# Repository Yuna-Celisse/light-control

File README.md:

# light-control

基于 KiCad 10 的 fNIRS 光学采集与灯光控制板工程。

当前原理图主控为 STM32F103C8T6，包含 USB-C 与 ESD 保护、3.3 V 降压和 1.8 V 电源、ADS1115、双 AS7341 光谱传感器，以及板载双路光电接收与双波长 LED 驱动电路。光谱模块承担系统中的其他检测用途。

## 打开工程

1. 安装 KiCad 10。本次主控迁移检查使用 KiCad 10.0.8。
2. 克隆仓库并打开 `light-control.kicad_pro`。
3. 通过项目管理器打开原理图和 PCB。
4. 安装 KiCad 标准符号及封装库。项目自定义库通过 `${KIPRJMOD}` 相对路径加载。此次新注册的部分标准库仍引用本机其他工程路径，迁移环境时须重新配置库路径。

## 文件结构

|路径|内容|
|---|---|
|`light-control.kicad_pro`|KiCad 项目|
|`light-control.kicad_sch`|顶层原理图|
|`01_*.kicad_sch` 至 `10_*.kicad_sch`|十张在用功能子页，主控使用 `03_stm32f103.kicad_sch`|
|`light-control.kicad_pcb`|四层 PCB，全板布线、铺铜与器件特性隐患修复已完成，待导出制板文件|
|`light-control.kicad_dru`|自定义设计规则|
|`FNIRS.pretty`、`Lights_Edge.pretty`|自定义封装|
|`FNIRS.kicad_sym`、`light-control-custom.kicad_sym`|自定义符号|
|`docs/review-2026-11-10.md`|设计变更、隐患修复与打样复核记录|
|`docs/checks`|检查证据（`drc.json`、`erc.json`、`source-sha256.txt`），须核对生成时间与对应设计版本|

## 当前验证状态

2026-11-17 完成全板布线、元器件特性隐患排查、走线几何规范化（含 `/03_STM32F103/NRST` 环路与锐角清理）及独立设计评审复核（当前包含 164 个器件、1459 段走线、223 个过孔、3 个铺铜区，`In1.Cu` 保持完整地平面且无信号线穿越）：

- **隐患修复与走线规范化**：已移除 `L1`、`D101`、`D103` 器件隐患并消除孤立 `GND` 铜岛；全板各层消除非 45°/90° 折线段、裸铜锐角、过孔中心 90° 拐角、冗余共线分段与重叠线段，将 `silk_over_copper` 警告清零（12 → 0），并移除 `NRST` 处 `C18.1`—`R9.2`—过孔同层闭合铜环与 45° 锐角及 `In2.Cu` 微线段。
- **DRC / ERC 与可制造性**：重填铺铜并保存后，KiCad 10.0.8 实测 **DRC 0 错误、0 未连接项**（仅剩 4 项库差异/字段警告：`lib_footprint_mismatch` ×3 与 `Y1` 缺少 `C0 max` 字段的 `schematic_parity` ×1）；**ERC 0 错误**（27 项既有 `lib_symbol_mismatch` 警告）；`validate_for_manufacturing` 结论为 **`READY`**（可打样，PCBA/改版前建议补齐 `F.Cu`/`B.Cu` Mark 点与 `U5` MPN、将 1 颗 `0.2 mm` 过孔统一为 `0.3 mm`、补齐电源测试点并将 `U4.~FAULT` 接入 MCU）。

2026-11-11 完成十个模块内部布线、地铜补接及工程文件清理，随后补全模块间互连；SWD 使用六个长方形表面焊盘（1.5 × 3 mm、中心距 2 mm）。

2026-11-10 已将原理图主控迁移至 STM32F103C8T6，补齐 VDD、VDDA、VBAT 去耦、BOOT0/BOOT1、NRST、SWD 和 USB D+ 1.5 kΩ 上拉。两组 I²C 分别连接 ADS1115 与左光谱模块、右光谱模块。主控页使用 12 MHz HSE，PLL ×6 对应 72 MHz，USB 分频 1.5 对应 48 MHz。

晶振选用 ABM8W-12.0000MHZ-6-D1X-T3，C38/C39 初配 6 pF，寄生电容暂按 3 pF 估计，最终负载需结合完成后的 PCB 与实测校准。

模块连线整理阶段覆盖 11 张在用原理图，模块内部采用连续导线，模块之间采用网络标签。整理前后 164 个器件的型号、数值、封装与 UUID 一致，全部网络端点连接一致。逐页导线检查为 0 个悬空端点，全项目 ERC 为 0 个错误、27 个库符号差异警告。

迁移前后导出网表对比显示，主控块以外的业务模块间连接一致。删除 ESP32 专用 L2、L3、C36，新增 J2 调试接口，其余主控外围按 STM32 重新配置。

PCB 已同步最新原理图，含 164 个器件。155 个原器件的位置、角度与层完全沿用原布局，U5 沿用原中心并旋转 90°，7 颗主控外围器件做了避让微调。J2 按参考图改为靠近板边的一排长方形表面焊盘，距板边 0.6 mm，间距 2 mm，单焊盘 1.5 × 3 mm，顺序为 3V3、SWDIO、GND、SWCLK、NRST、GND。

最终 DRC/ERC 报告及核查明细见 [复核记录](docs/review-2026-11-10.md) 与 [`docs/checks/`](docs/checks)。

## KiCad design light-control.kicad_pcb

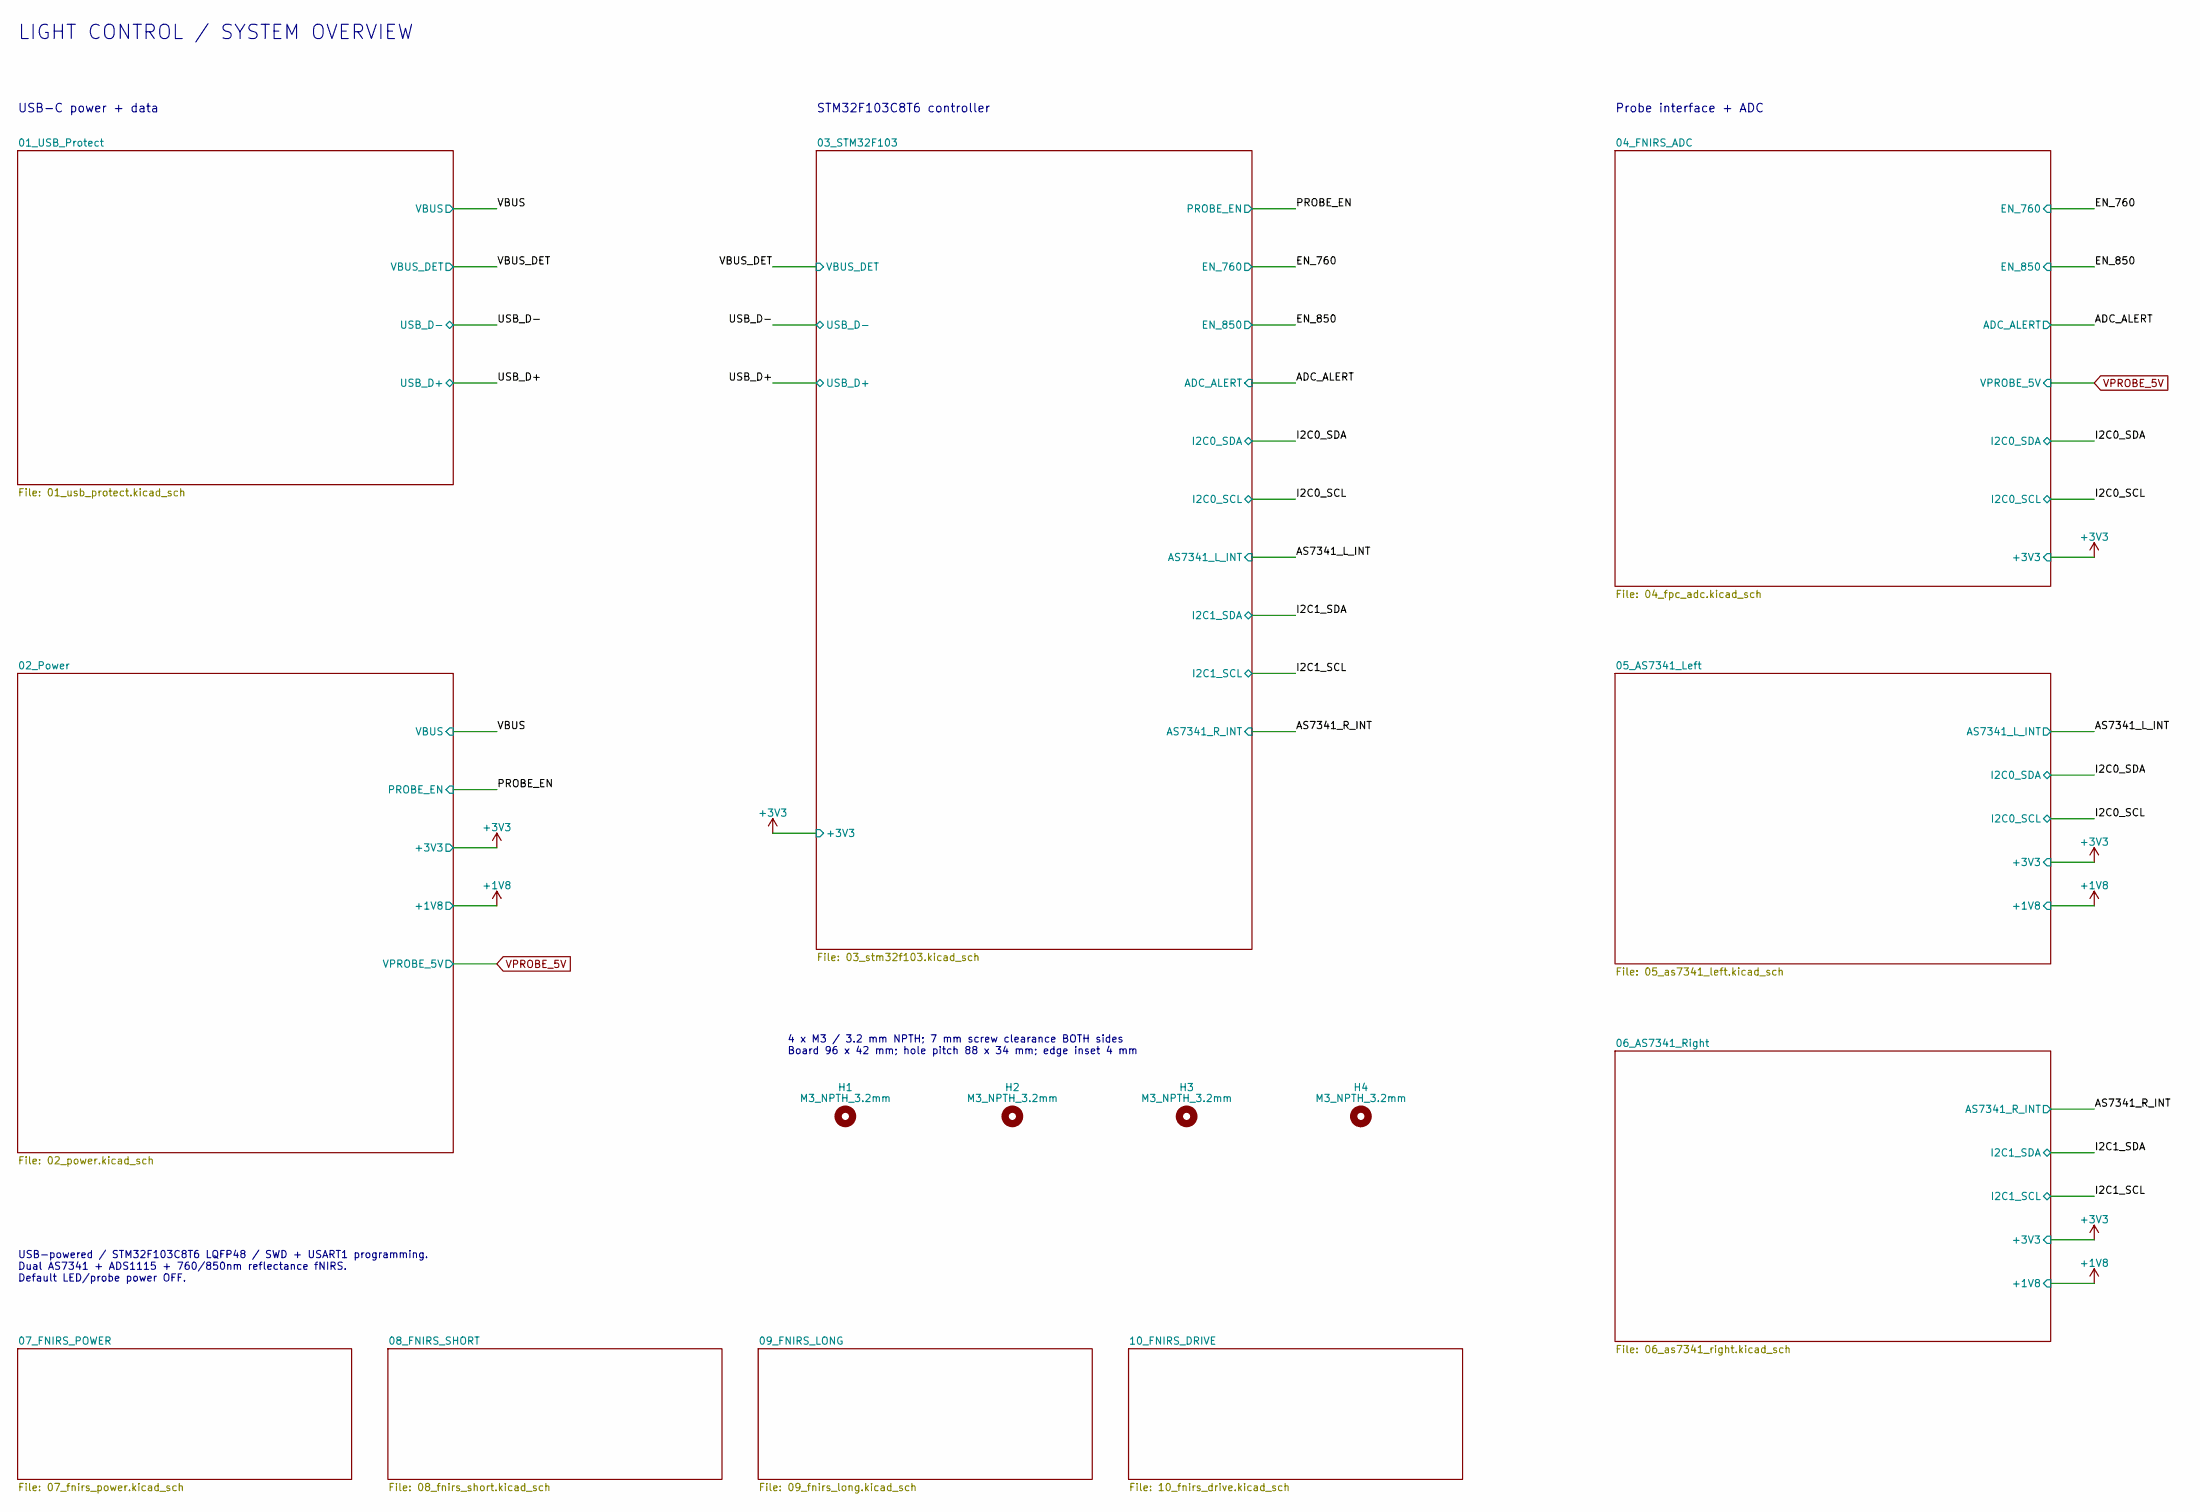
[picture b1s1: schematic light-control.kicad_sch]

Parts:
H1, H2, H3, H4: M3_NPTH_3.2mm; MountingHole_M3_3.2mm_Clearance7mm

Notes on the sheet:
LIGHT CONTROL / SYSTEM OVERVIEW
4 x M3 / 3.2 mm NPTH; 7 mm screw clearance BOTH sides Board 96 x 42 mm; hole pitch 88 x 34 mm; edge inset 4 mm
Probe interface + ADC
USB-C power + data
STM32F103C8T6 controller
USB-powered / STM32F103C8T6 LQFP48 / SWD + USART1 programming. Dual AS7341 + ADS1115 + 760/850nm reflectance fNIRS. Default LED/probe power OFF.

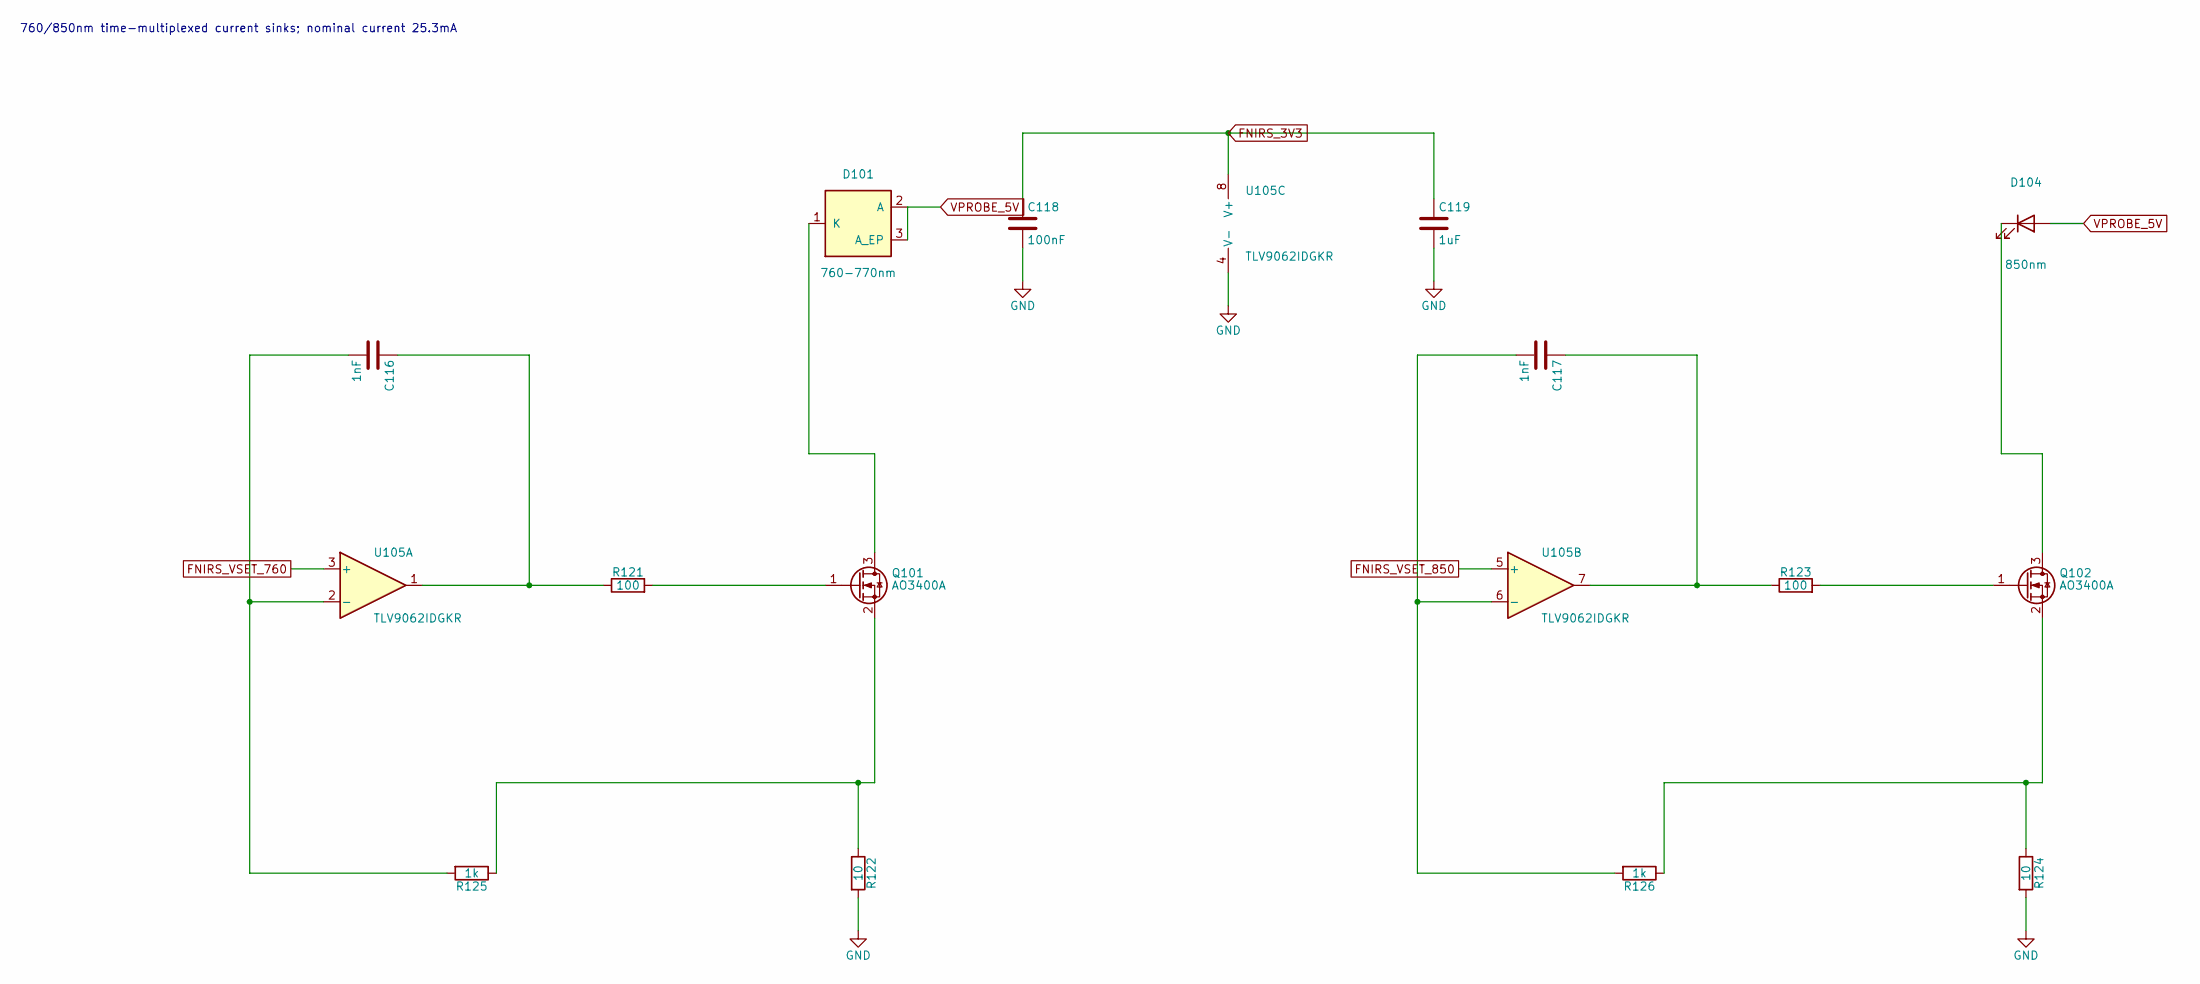
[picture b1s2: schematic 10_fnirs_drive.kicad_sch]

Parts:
C116, C117: 1nF; C_0603_1608Metric; MPN CL10C102JB8NNNC
C118: 100nF; C_0603_1608Metric
C119: 1uF; C_0603_1608Metric
D101: 760-770nm; JNJ_760_3535_3P; MPN JNJ-LEHR0113W120/42MIL/760-770NM
D104: 850nm; JNJ_850_3036_2P; MPN JNJ-LTJI0106W90/14mil-D/850NM
Q101, Q102: AO3400A; SOT-23; MPN AO3400A
R121, R123: 100; R_0603_1608Metric; MPN 0603WAF1000T5E
R122, R124: 10; R_0603_1608Metric; MPN 0603WAF100JT5E
R125, R126: 1k; R_0603_1608Metric; MPN 0603WAF1001T5E
U105: TLV9062IDGKR; VSSOP-8_3x3mm_P0.65mm; MPN TLV9062IDGKR

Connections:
FNIRS_3V3: C118.1, C119.1, U105.8 (V+); also elsewhere on the board
FNIRS_VSET_760: U105.3 (+); also elsewhere on the board
FNIRS_VSET_850: U105.5 (+); also elsewhere on the board
unnamed: C116.1, R121.1, U105.1
unnamed: C117.1, R123.1, U105.7
unnamed: D101.1 (K), Q101.3 (D)
unnamed: D104.1 (K), Q102.3 (D)
unnamed: Q101.1 (G), R121.2
unnamed: Q101.2 (S), R122.1, R125.1
unnamed: Q102.1 (G), R123.2
unnamed: Q102.2 (S), R124.1, R126.1
unnamed: C116.2, R125.2, U105.2 (-)
unnamed: C117.2, R126.2, U105.6 (-)
VPROBE_5V: D101.2 (A), D101.3 (A_EP), D104.2 (A); also elsewhere on the board

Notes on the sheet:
760/850nm time-multiplexed current sinks; nominal current 25.3mA

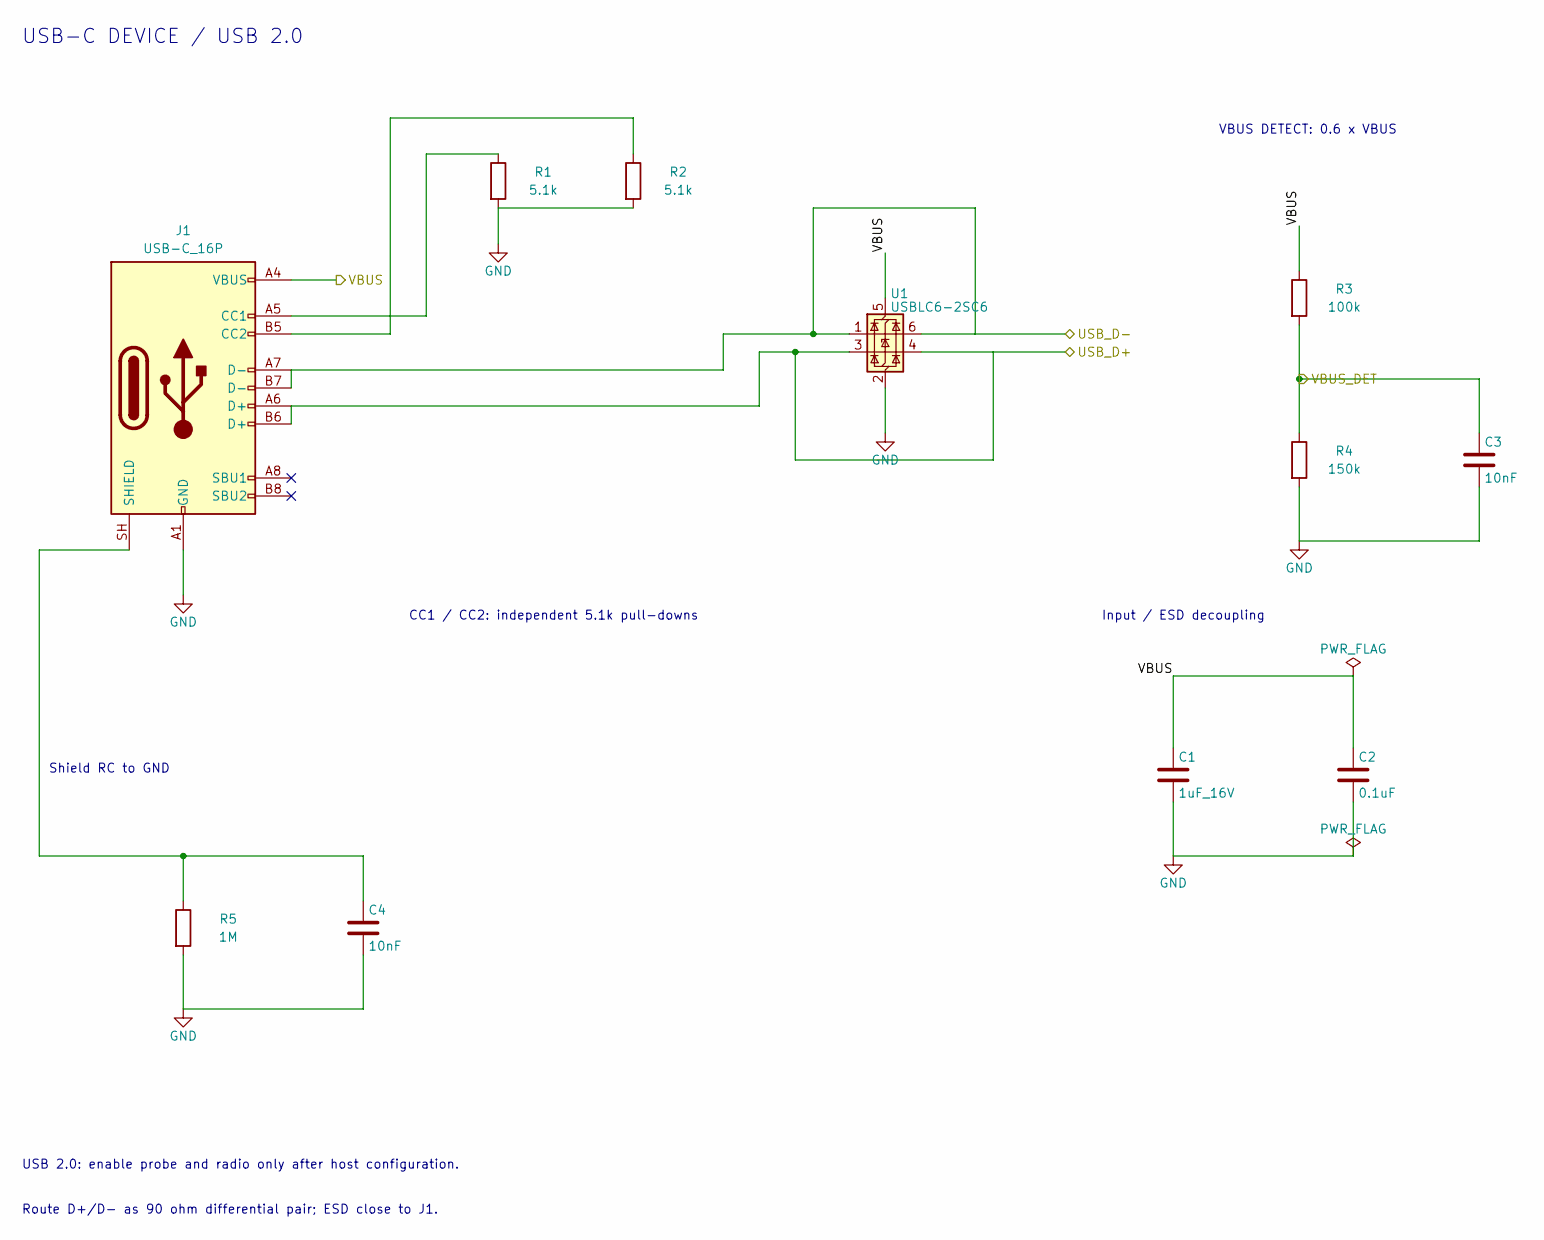
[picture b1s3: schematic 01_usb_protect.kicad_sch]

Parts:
C1: 1uF_16V; C_0603_1608Metric
C2: 0.1uF; C_0402_1005Metric
C3: 10nF; C_0402_1005Metric
C4: 10nF; C_0603_1608Metric
J1: USB-C_16P; USB_C_Receptacle_HRO_TYPE-C-31-M-12
R1, R2: 5.1k; R_0402_1005Metric
R3: 100k; R_0402_1005Metric
R4: 150k; R_0402_1005Metric
R5: 1M; R_0603_1608Metric
U1: USBLC6-2SC6; SOT-23-6; MPN USBLC6-2SC6

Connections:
/USB_D+: J1.A6 (D+), J1.B6 (D+), U1.3 (I/O2), U1.4 (I/O2); also elsewhere on the board
/USB_D-: J1.A7 (D-), J1.B7 (D-), U1.1 (I/O1), U1.6 (I/O1); also elsewhere on the board
/VBUS_DET: C3.1, R3.2, R4.1; also elsewhere on the board
unnamed: J1.A5 (CC1), R1.1
unnamed: J1.B5 (CC2), R2.1
unnamed: C4.1, J1.SH (SHIELD), R5.1

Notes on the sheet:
Shield RC to GND
VBUS DETECT: 0.6 x VBUS
USB-C DEVICE / USB 2.0
CC1 / CC2: independent 5.1k pull-downs
Input / ESD decoupling
Route D+/D- as 90 ohm differential pair; ESD close to J1.
USB 2.0: enable probe and radio only after host configuration.

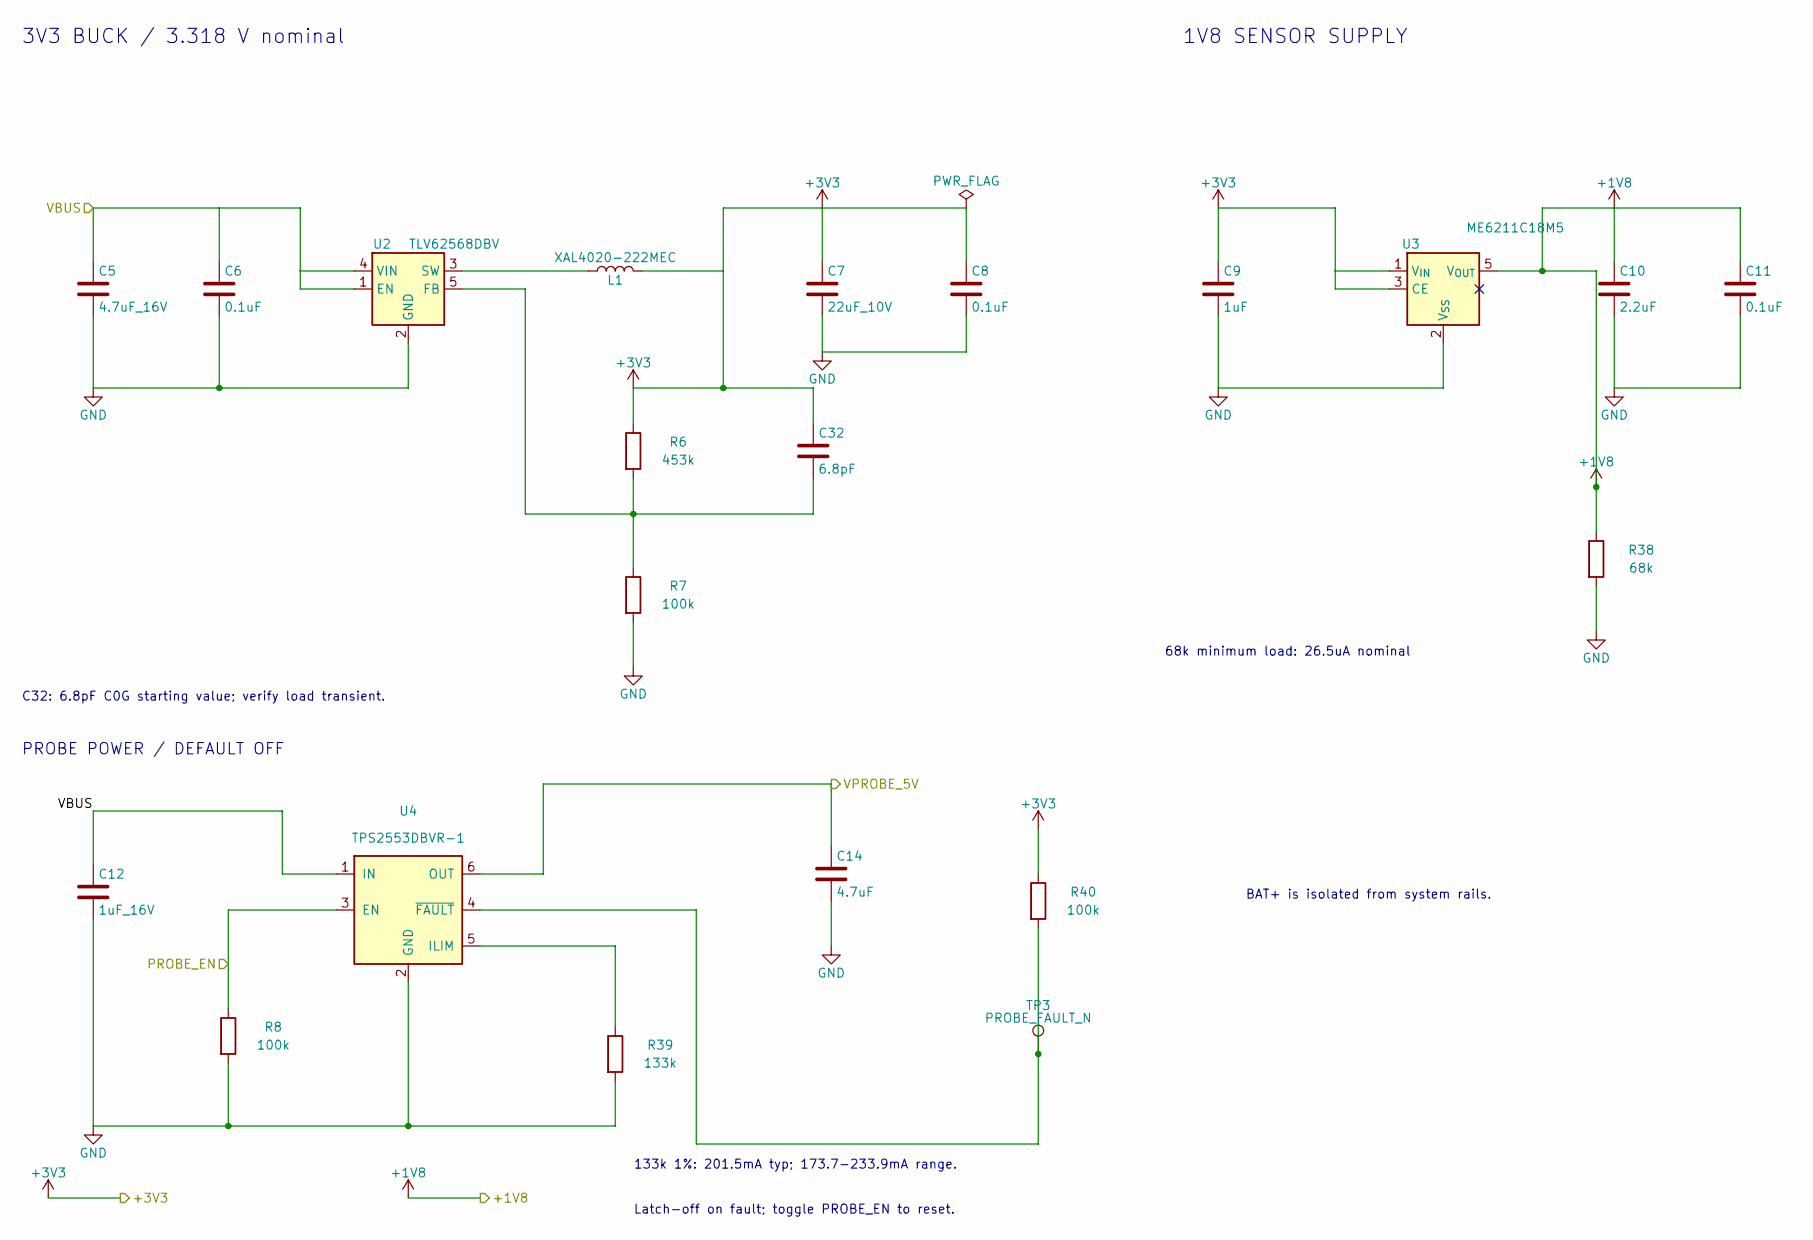
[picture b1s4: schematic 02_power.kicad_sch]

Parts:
C5: 4.7uF_16V; C_0805_2012Metric
C6, C8, C11: 0.1uF; C_0402_1005Metric
C7: 22uF_10V; C_0805_2012Metric
C9: 1uF; C_0402_1005Metric
C10: 2.2uF; C_0603_1608Metric
C12: 1uF_16V; C_0402_1005Metric
C14: 4.7uF; C_0603_1608Metric
C32: 6.8pF; C_0402_1005Metric; Tolerance 5%
L1: XAL4020-222MEC; L_Coilcraft_XAL4020-XXX
R6: 453k; R_0402_1005Metric
R7, R8, R40: 100k; R_0402_1005Metric
R38: 68k; R_0402_1005Metric; Tolerance 1%
R39: 133k; R_0402_1005Metric; Tolerance 1%
TP3: PROBE_FAULT_N; TestPoint_Pad_D1.0mm
U2: TLV62568DBV; SOT-23-5; MPN TLV62568DBVR
U3: ME6211C18M5; SOT-23-5; MPN ME6211C18M5
U4: TPS2553DBVR-1; SOT-23-6; MPN TPS2553DBVR-1

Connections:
+1V8: C10.1, C11.1, R38.1, U3.5 (V_{OUT}); also elsewhere on the board
+3V3: C7.1, C8.1, C9.1, C32.1, L1.2, R6.1, R40.1, U3.1 (V_{IN}), U3.3 (CE); also elsewhere on the board
/PROBE_EN: R8.1, U4.3 (EN); also elsewhere on the board
unnamed: C32.2, R6.2, R7.1, U2.5 (FB)
unnamed: L1.1, U2.3 (SW)
unnamed: R39.1, U4.5 (ILIM)
unnamed: R40.2, TP3.1 (1_1), U4.4 (~FAULT)
VPROBE_5V: C14.1, U4.6 (OUT); also elsewhere on the board

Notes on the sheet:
3V3 BUCK / 3.318 V nominal
BAT+ is isolated from system rails.
Latch-off on fault; toggle PROBE_EN to reset.
C32: 6.8pF C0G starting value; verify load transient.
PROBE POWER / DEFAULT OFF
133k 1%: 201.5mA typ; 173.7-233.9mA range.
68k minimum load: 26.5uA nominal
1V8 SENSOR SUPPLY

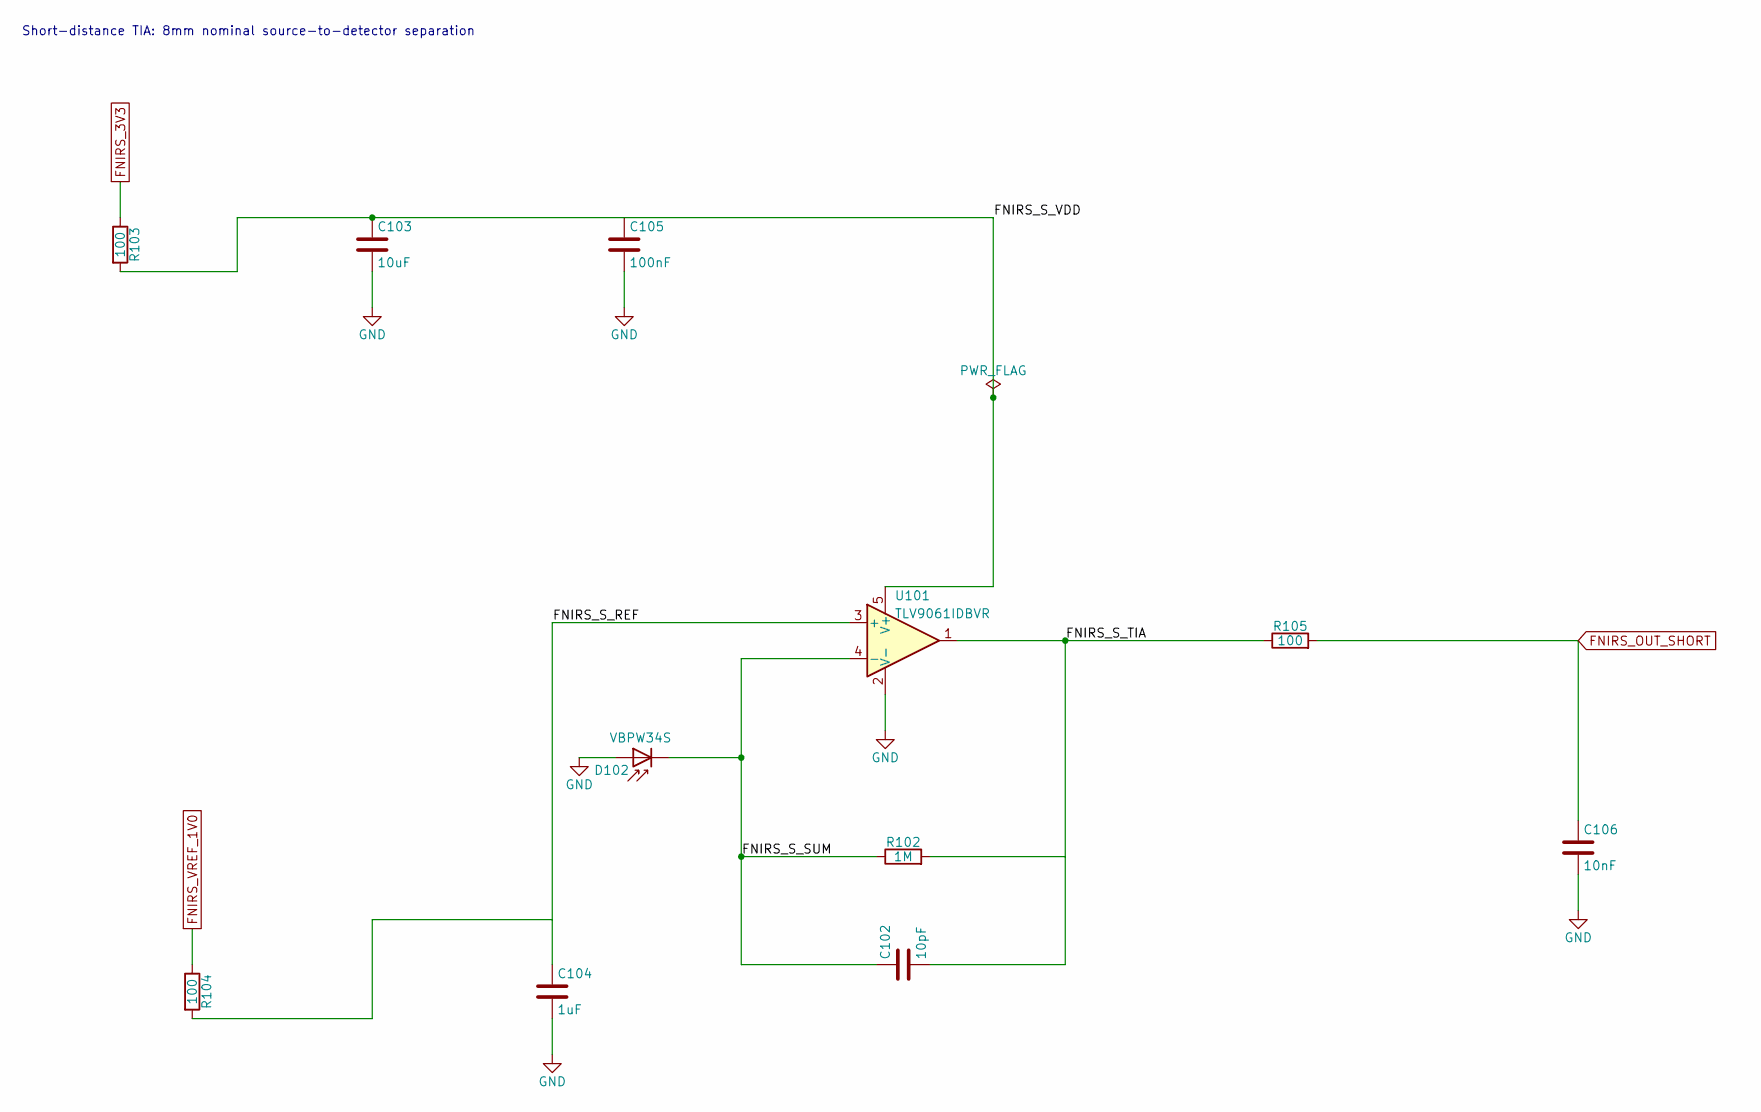
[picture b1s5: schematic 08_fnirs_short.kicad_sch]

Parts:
C102: 10pF; C_0603_1608Metric; MPN CL10C100JB8NNNC
C103: 10uF; C_0805_2012Metric; MPN CL21A106KAYNNNE
C104: 1uF; C_0603_1608Metric; MPN CL10A105KB8NNNC
C105: 100nF; C_0603_1608Metric; MPN CC0603KRX7R9BB104
C106: 10nF; C_0603_1608Metric; MPN 0603B103K500NT
D102: VBPW34S; VBPW34S_Normal_Gullwing; MPN VBPW34S
R102: 1M; R_0603_1608Metric; MPN 0603WAF1004T5E
R103, R104, R105: 100; R_0603_1608Metric; MPN 0603WAF1000T5E
U101: TLV9061IDBVR; SOT-23-5; MPN TLV9061IDBVR

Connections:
/08_FNIRS_SHORT/FNIRS_S_REF: C104.1, R104.2, U101.3 (+)
/08_FNIRS_SHORT/FNIRS_S_SUM: C102.1, D102.1 (K), R102.1, U101.4 (-)
/08_FNIRS_SHORT/FNIRS_S_TIA: C102.2, R102.2, R105.1, U101.1
/08_FNIRS_SHORT/FNIRS_S_VDD: C103.1, C105.1, R103.2, U101.5 (V+)
FNIRS_3V3: R103.1; also elsewhere on the board
FNIRS_OUT_SHORT: C106.1, R105.2; also elsewhere on the board
FNIRS_VREF_1V0: R104.1; also elsewhere on the board

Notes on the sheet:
Short-distance TIA: 8mm nominal source-to-detector separation

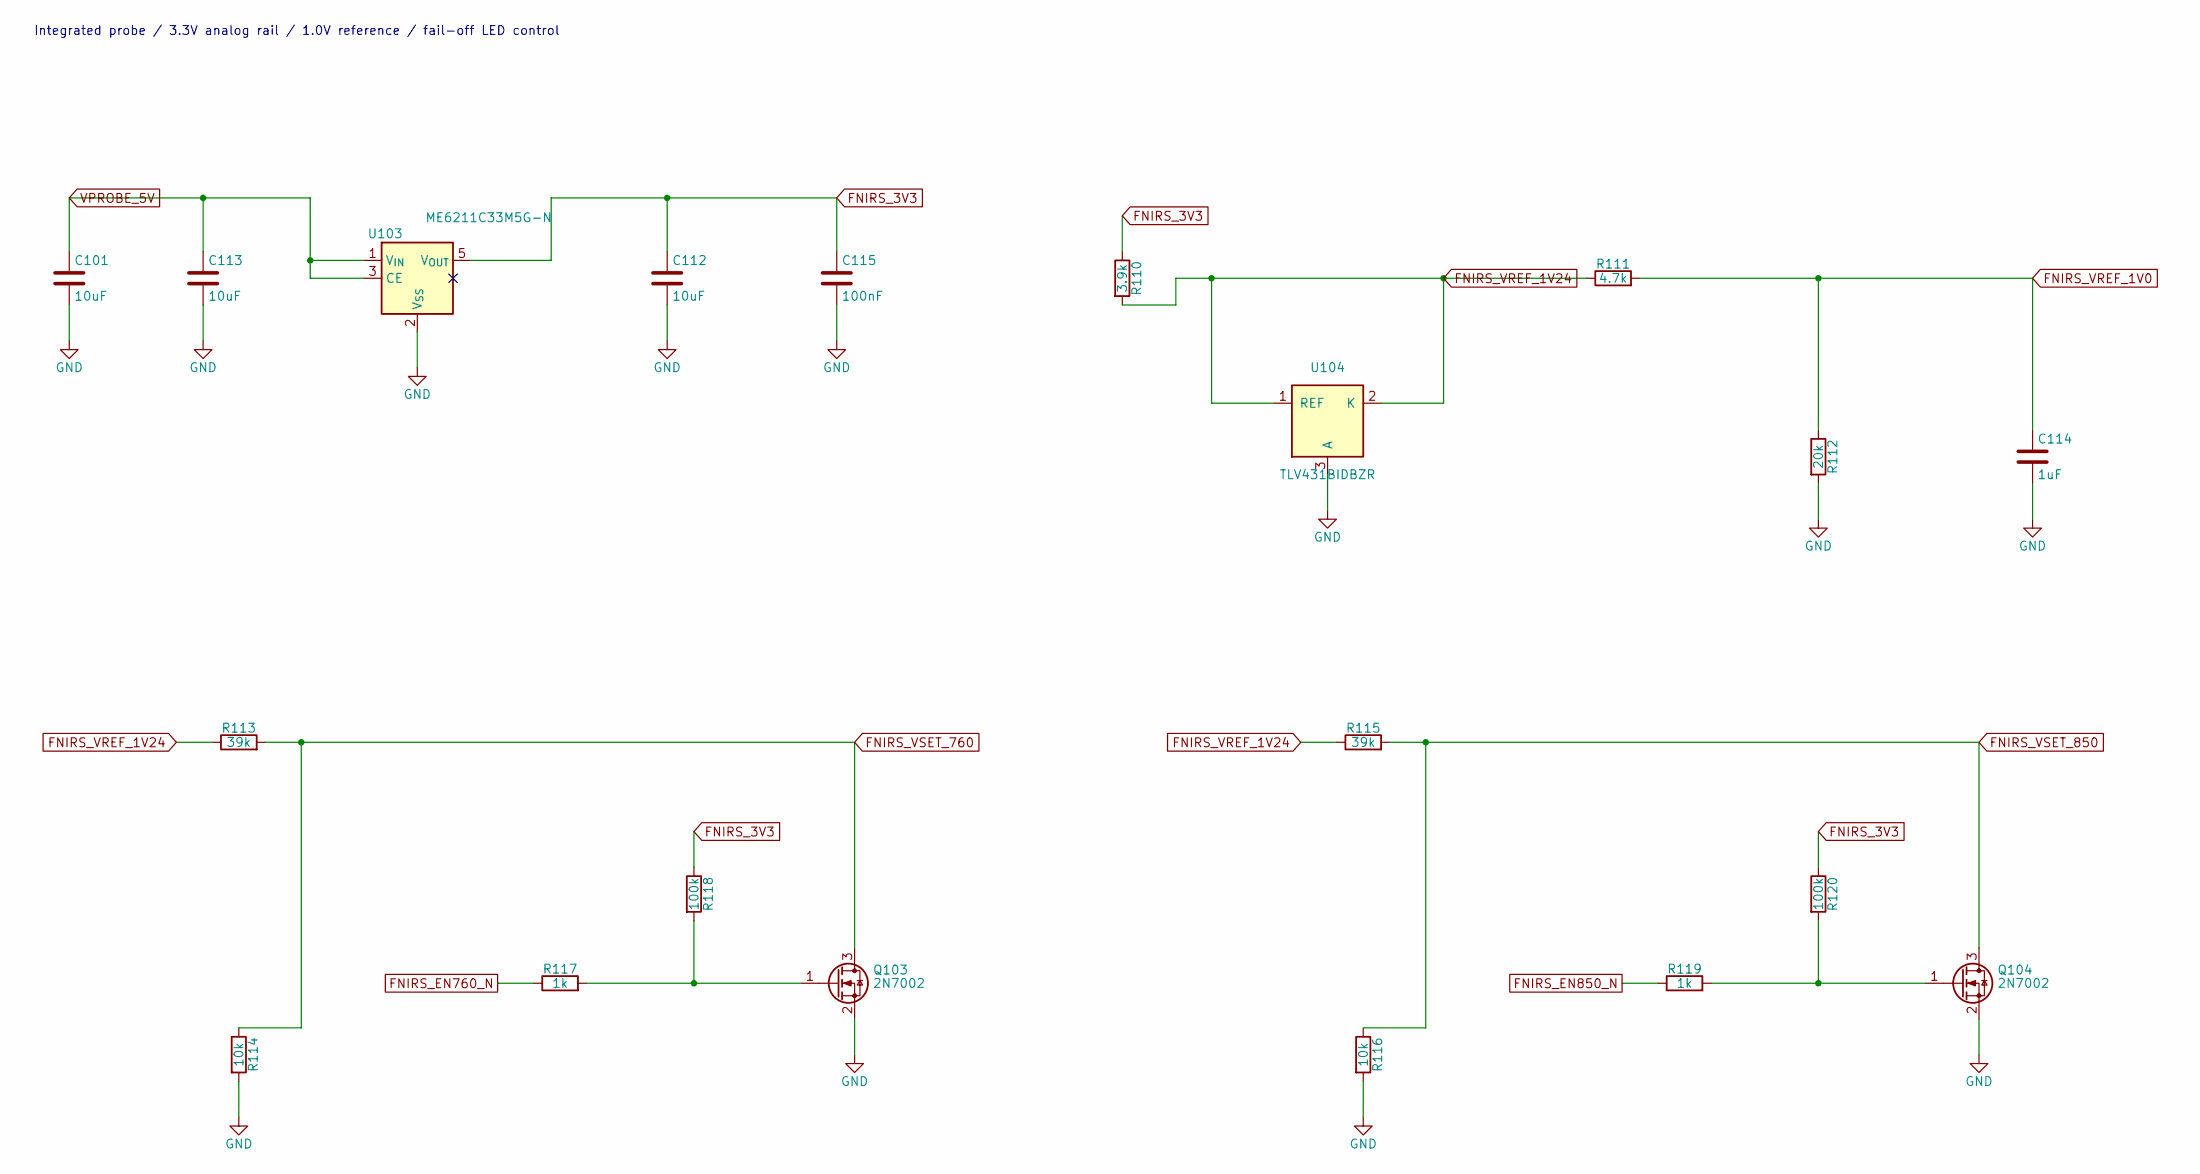
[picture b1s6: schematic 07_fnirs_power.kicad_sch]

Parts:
C101, C112, C113: 10uF; C_0805_2012Metric; MPN CL21A106KAYNNNE
C114: 1uF; C_0603_1608Metric; MPN CL10A105KB8NNNC
C115: 100nF; C_0603_1608Metric; MPN CL10B104KB8NNNC
Q103, Q104: 2N7002; SOT-23; MPN 2N7002
R110: 3.9k; R_0603_1608Metric; MPN 0603WAF3901T5E
R111: 4.7k; R_0603_1608Metric; MPN 0603WAF4701T5E
R112: 20k; R_0603_1608Metric; MPN 0603WAF2002T5E
R113, R115: 39k; R_0603_1608Metric; MPN 0603WAF3902T5E
R114, R116: 10k; R_0603_1608Metric; MPN 0603WAF1002T5E
R117, R119: 1k; R_0603_1608Metric; MPN 0603WAF1001T5E
R118, R120: 100k; R_0603_1608Metric; MPN 0603WAF1003T5E
U103: ME6211C33M5G-N; SOT-23-5; MPN ME6211C33M5G-N
U104: TLV431BIDBZR; SOT-23; MPN TLV431BIDBZR

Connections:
FNIRS_3V3: C112.1, C115.1, R110.1, R118.1, R120.1, U103.5 (V_{OUT}); also elsewhere on the board
FNIRS_EN760_N: R117.1; also elsewhere on the board
FNIRS_EN850_N: R119.1; also elsewhere on the board
FNIRS_VREF_1V0: C114.1, R111.2, R112.1; also elsewhere on the board
FNIRS_VREF_1V24: R110.2, R111.1, R113.1, R115.1, U104.1 (REF), U104.2 (K)
FNIRS_VSET_760: Q103.3 (D), R113.2, R114.1; also elsewhere on the board
FNIRS_VSET_850: Q104.3 (D), R115.2, R116.1; also elsewhere on the board
unnamed: Q103.1 (G), R117.2, R118.2
unnamed: Q104.1 (G), R119.2, R120.2
VPROBE_5V: C101.1, C113.1, U103.1 (V_{IN}), U103.3 (CE); also elsewhere on the board

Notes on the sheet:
Integrated probe / 3.3V analog rail / 1.0V reference / fail-off LED control

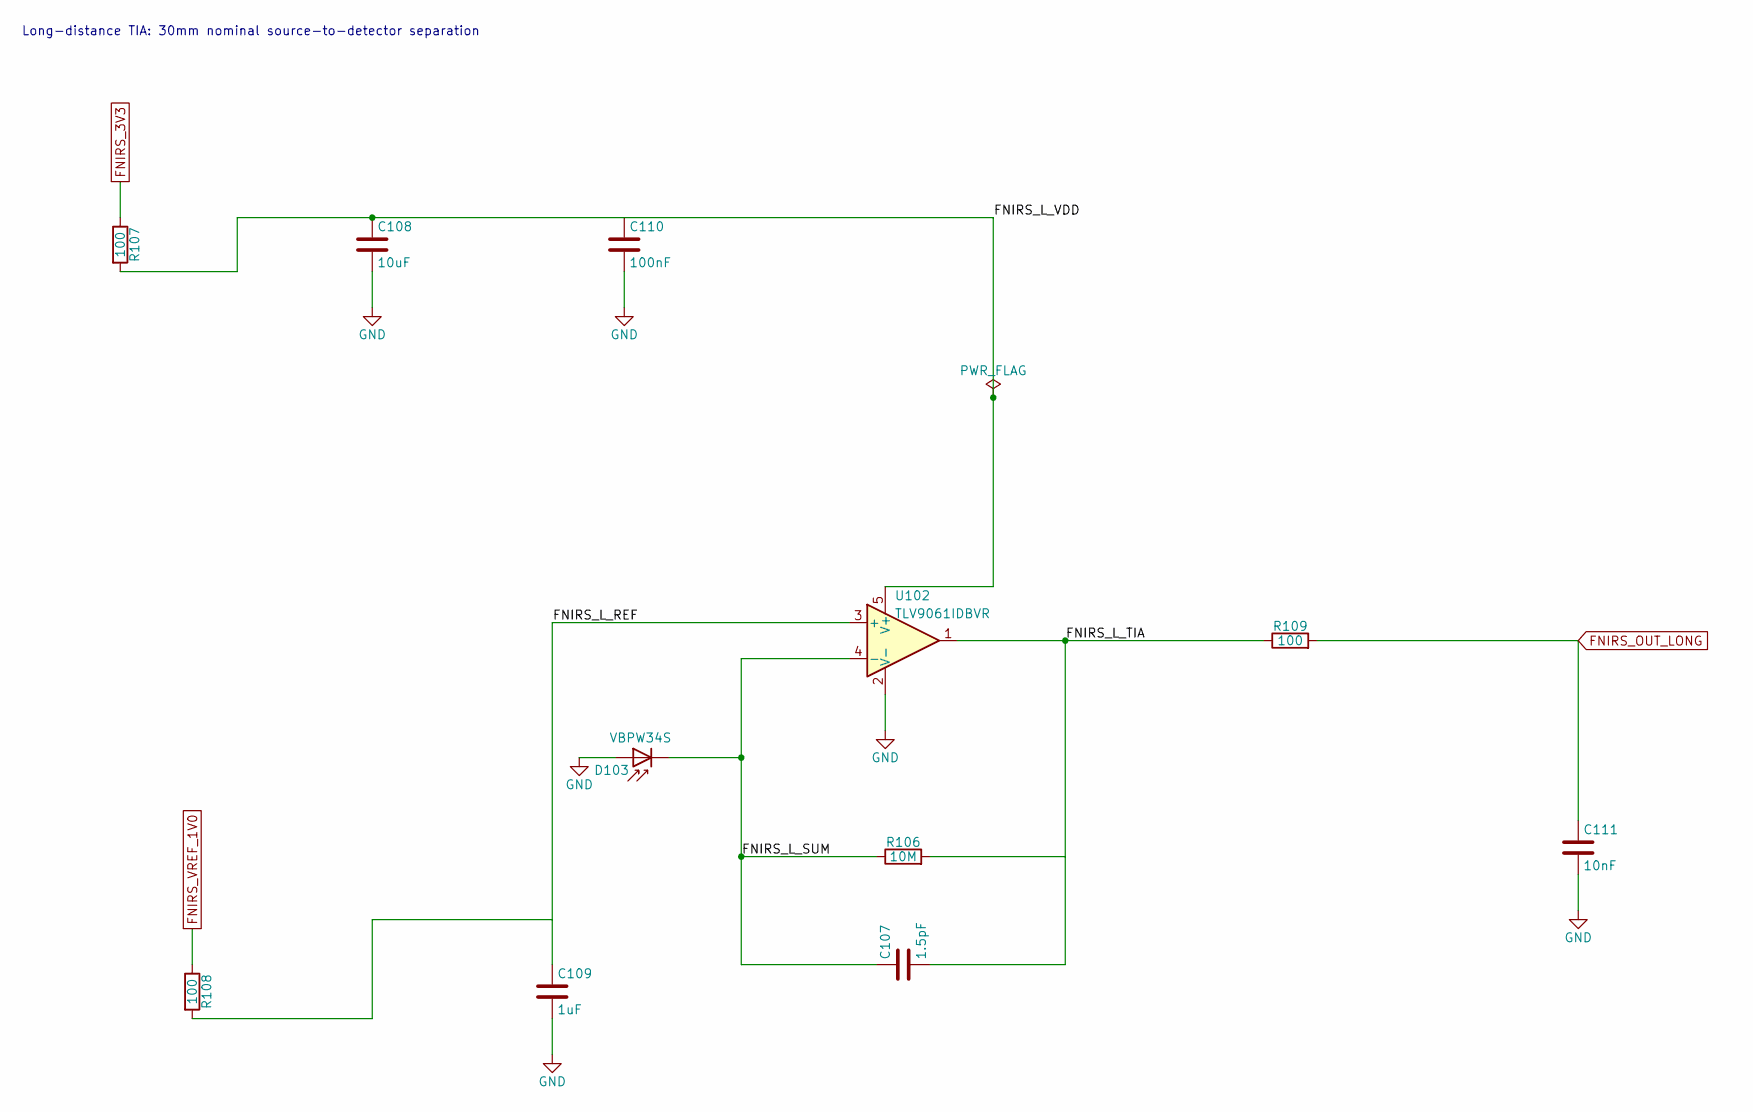
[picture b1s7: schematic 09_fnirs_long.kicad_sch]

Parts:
C107: 1.5pF; C_0603_1608Metric; MPN CL10C1R5BB8NNNC
C108: 10uF; C_0805_2012Metric; MPN CL21A106KAYNNNE
C109: 1uF; C_0603_1608Metric; MPN CL10A105KB8NNNC
C110: 100nF; C_0603_1608Metric; MPN CC0603KRX7R9BB104
C111: 10nF; C_0603_1608Metric; MPN 0603B103K500NT
D103: VBPW34S; VBPW34S_Normal_Gullwing; MPN VBPW34S
R106: 10M; R_0603_1608Metric; MPN 0603WAF1005T5E
R107, R108, R109: 100; R_0603_1608Metric; MPN 0603WAF1000T5E
U102: TLV9061IDBVR; SOT-23-5; MPN TLV9061IDBVR

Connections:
/09_FNIRS_LONG/FNIRS_L_REF: C109.1, R108.2, U102.3 (+)
/09_FNIRS_LONG/FNIRS_L_SUM: C107.1, D103.1 (K), R106.1, U102.4 (-)
/09_FNIRS_LONG/FNIRS_L_TIA: C107.2, R106.2, R109.1, U102.1
/09_FNIRS_LONG/FNIRS_L_VDD: C108.1, C110.1, R107.2, U102.5 (V+)
FNIRS_3V3: R107.1; also elsewhere on the board
FNIRS_OUT_LONG: C111.1, R109.2; also elsewhere on the board
FNIRS_VREF_1V0: R108.1; also elsewhere on the board

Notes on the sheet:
Long-distance TIA: 30mm nominal source-to-detector separation
